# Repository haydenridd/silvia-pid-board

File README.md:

# Rancilio Silvia PID Board

A hardware and firmware project for adding PID boiler control to a stock Rancilio Silvia espresso machine.

## Obligatory Disclaimer

This project involves working with mains voltage as well as high power output heaters! Mains voltage *can kill or
seriously injure you* and improper control of an ~850W heating element *can start fires*. This project is provided
as-is with no regulatory certifications or guarantees of safety. It is on the user to do their due diligence in
ensuring their own safety, as well as the safe modification and operation of the espresso machine.

## Motivation

Adding PID heater control to the Rancilio Silvia is a popular mod, however it usually involves adding a
standalone PID controller like [this](https://www.auberins.com/index.php?main_page=product_info&products_id=36) to the
exterior of the machine. I've also seen a
number of great write-ups on home-brew mods \(so to speak\) like [this](https://misssilviapi.wordpress.com/) and
[this](https://int03.co.uk/blog/project-coffee-espiresso-machine/). However, many of the mods have
gravitated towards using various parts and modules found on Amazon, and are generally fairly invasive to the machine
itself (modules on the outside, cutting into the chassis, etc).

I had two goals with this project:
- Design a robust PID control board and source components entirely from a reputable distributor (DigiKey in this case)
- Design the board in such a way that it fits inside the machine, and leaves the control of the machine unchanged

### A Brief Aside on Amazon Parts
At the time of this writing, the electrical engineer in me would *not* consider Amazon to be a reputable retailer
for electronic parts. There have been many [reports](https://www.coffeeforums.co.uk/threads/gaggia-classic-pid-owners-watch-out-for-counterfeit-ssrs-on-ebay-amazon-etc.61314/)
of [fake parts](https://squashpractice.com/2024/01/01/counterfeits-parts-ebay-scammers-and-amazon-shills/) coming from
Amazon across all corners of industry. While these are generally ~half the price of the part they're
knocking off, you have essentially no recourse or accountability should this part fail in a catastrophic way. And
when it comes to switching AC mains and high powered heaters, that was not a gamble I was willing to take. This
project sources its parts entirely from DigiKey with the exception of a custom RTD sensor for the boiler.

## Design Ethos

I love the chunky, tactile feel of the stock Silvia machine. I wanted to leave how you control the machine entirely
unchanged. This is NOT a total conversion mod like the [Gagguino](https://gaggiuino.github.io/#/) although that project
is certainly cool. Post-mod, the machine still looks and functions largely the same to the external user, with a
small exception being how I use the heating lamp to indicate temperature status.

## Hardware Design

See [the hardware README](./silvia_pid_board/README.md) for a detailed breakdown of the electronic design, parts list,
and hookup diagram. This diagram shows the high-level design of the board:

The board, in a hacky chip board "enclosure", fits snugly in between the steam valve and the leftmost control switches:

## Firmware Design

A Raspberry Pi Pico was used for the microcontroller driving the hardware because they're cheap, and extremely well
documented. The firmware is written in [Zig](https://ziglang.org/), a fantastic up-and-coming language that I've
fallen in love with for low-level firmware development. See [the firmware README](./firmware/README.md) for more
details.

## Performance

The following shows the temperature behavior of the thermostat style regulation that comes with a stock Silvia. 

A graph of temperature over time at the espresso temperature setpoint:

And a graph of temperature of time at the steam temperature setpoint:

Compare this to the new PID regulation at the espresso setpoint:

And regulation at the steam setpoint:

Where the red line is temperature, and the blue line is duty cycle of the heater. Both of these plots can be produced
with a [script](firmware/scripts/graph_temperature.py) in the firmware folder. See that README for more details on
data logging + plotting.

Espresso setpoint regulation is extremely tight, generally regulating to within 1C. Steam regulation generally sits
~2C below the setpoint of 145C, but experimentally I found this to produce nice milk steaming pressure. Both setpoints were chosen based
on the behavior of the original thermostat + some experimental tweaking. It should be noted temperature is measured
at the exterior of the boiler, meaning a setpoint of 108C does *not* mean 108C water is going through your
espresso puck. 

## Building Your Own

All the tools you need to make one of these modules yourself are provided in this repository. I used JLPCB to build the
boards, however the gerber files located in `silvia_pid_board/board_gerbers` can be used to build boards at a PCB
fab of your preference. Note though that design rules were checked according to JLPCB's capabilities. The KiCAD design
files are also available in `silvia_pid_board` should you want to modify the board or run different design rule checks.

At the time of writing, the total BOM cost of the Digikey parts is $34. Should you choose to use the same RTD module
costing $28, and JLPCB for your fab costing ~$30 with shipping, and add some cash for shipping from Digikey, the total
cost sits ~$100 for a buildout of this. Pretty good considering an off the shelf module is ~$150! I've included the 
Digikey part numbers with the [parts list](./silvia_pid_board/parts_list.csv) where relevant, so ordering parts for
this build should be fairly straightforward.

## Closing Thoughts and Areas of Improvement

This repo is unlikely to see any major updates, and mostly serves as a write-up/how-to for anyone looking to replicate
or expand upon this project. In its current state, it does exactly what I want for my machine. However, here are some
minor things I would change if I were to do another revision of the board/firmware:
- Add a standardized SWD header to the board + route corresponding signals from the Pico for easier debugger
connection
- Solder the RP2040 + required supporting ICs directly to the board to save space rather than using the Pico board
- Add CAD designs for a 3D printable enclosure
- Implement a serial port via a USB endpoint, removing the need for a dedicated UART connection
- Expand on the CLI and logging capabilities

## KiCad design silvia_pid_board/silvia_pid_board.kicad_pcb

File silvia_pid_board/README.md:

# Hardware Design

The following outlines:
- Board circuit design
- Hookup/wiring guide
- Board mounting
- BOM/Fabrication info

## Circuit Design

A PDF of the board schematic can be found [here](./silvia_pid_board.pdf), and is useful for following along with
circuit design discussion. The circuit design for this board can be broken into the following components:
- Power supply
- AC mains switching for the boiler
- AC mains detection from the steam switch
- Heating LED control

Note that this PCB was designed with a 120VAC/60Hz mains supply in mind, and that a careful design review should be
conducted if a user wants to adapt this to a different mains input (for instance 220VAC).  

### Power Supply

Extremely simple and easy, as it is a single component, the [IRM-05](https://www.meanwellusa.com/upload/pdf/IRM-05/IRM-05-spec.pdf).
While you could probably design a switched power supply that produces 5V from AC mains voltage for a little cheaper (this part costs $7),
this part simplified a lot of headaches. Does exactly as advertised, produces a clean 5V DC from 120 VAC delivering up
to 5W of power.

### AC Mains Switching

I spent the most time and intention on this part of the design, and switching AC to the boiler (to heat it) is
accomplished with the following circuit:

This was carefully designed based on the [following application note](https://www.st.com/resource/en/application_note/an5114-controlling-a-triac-with-a-phototriac-stmicroelectronics.pdf)
from ST Micro. I will be the first to admit it's over-engineered, as it almost certainly doesn't need a snubber circuit
given it's a simple resistive load being switched. One should note that the opto-coupler used is zero-crossing, meaning
no matter when the MCU goes to switch the heater on/off, it will only switch at the zero crossing point of the AC waveform.
Note you can only switch the heater on/off as fast as the frequency of the AC input (60Hz for US), however given the
duty period of the control loop is slow (one second) it doesn't matter.

The triac used for switching is passively cooled using a board mounted heatsink. Note that experimentally this has
been plenty effective for dissapating heat, but that a redesign is likely in order if switching a higher power heater
than the Silvia's.

### AC Mains Detection

This was entirely in service of allowing the steam switch to still turn on its own integrated AC powered lamp when it
switches on/off. The following circuit:

Detects when the steam switch has been flipped "on" by detecting an AC signal. The [FOD814S](https://www.onsemi.com/download/data-sheet/pdf/fod814-d.pdf)
makes this quite easy. The `LINE_ZEROCROSS_SENSE` signal will end up being pulled to ground every time the AC signal
is over the turn-on voltage of the in-package photo-diodes. See the [firmware README](../firmware/README.md) for more
details on how this signal is used.

### Heating LED Control

The lower lamp on the power switched that is used as a heating indicator in the stock Silvia is replace by a white LED
controlled by the microcontroller. The dimensions of the chosen LED are quite similar to the stock lamp, so it was quite
easy to replace the stock lamp while preserving its housing and orange jewel lens. See the [firmware README](../firmware/README.md)
for more info on how this is used, but the general idea is a solid LED means "off target", a pulsing LED means
"close to target", and an off LED means "at target". 

## Hookup/Wiring Guide

The following is an annotated version of the electrical diagram provided with the Silvia's manual. It shows which
electrical connections have been removed or re-routed, and which signals they connect to on the PCB.

18 gauge wire was used for all AC signal level connections, and 22 gauge wire was used for all MCU signal
level connections (RTD sensor and LED).

## Board Mounting + Enclosure

Mounting holes are provided in the PCB to accomodate M3 size screws. I ended up using nylon standoffs and screws to
sandwich the board between two pieces of thick card-stock like material. 

## BOM/Fabrication

See [the following CSV](./parts_list.csv) for a full parts list for the project. The "Notes" column details whether the part goes on the
board itself, or is an ancillary part used for connections/etc.

The gerber files for getting this board fabricated are located in [board_gerbers](./board_gerbers), and pass the design
rules in `silvia_pid_board.kicad_dru` (provided by JLPCB).

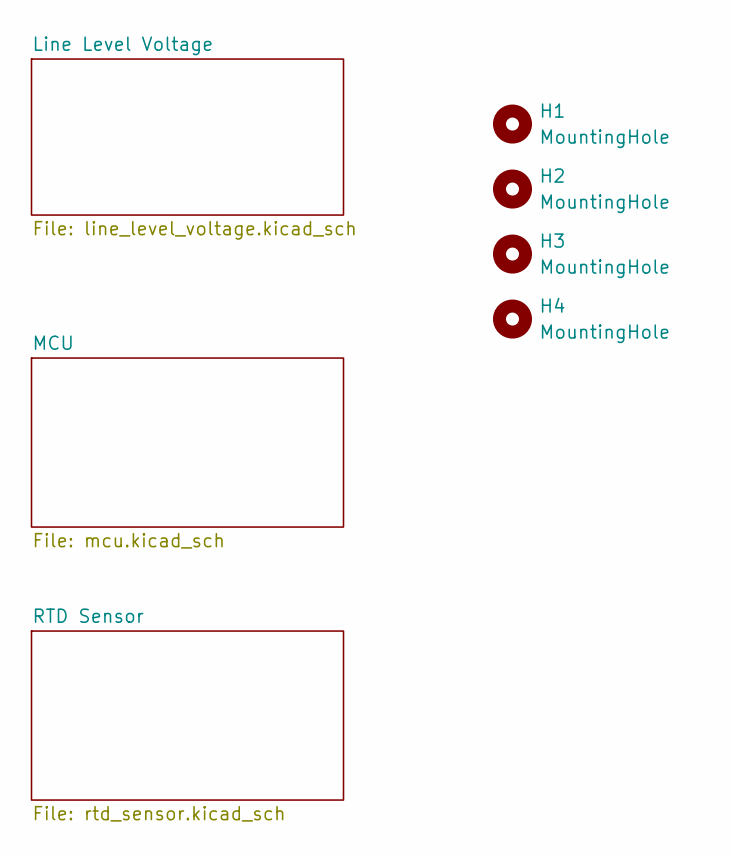
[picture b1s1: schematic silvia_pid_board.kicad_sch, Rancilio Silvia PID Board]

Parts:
H1, H2, H3, H4: MountingHole; MountingHole_3.2mm_M3_Pad_TopOnly

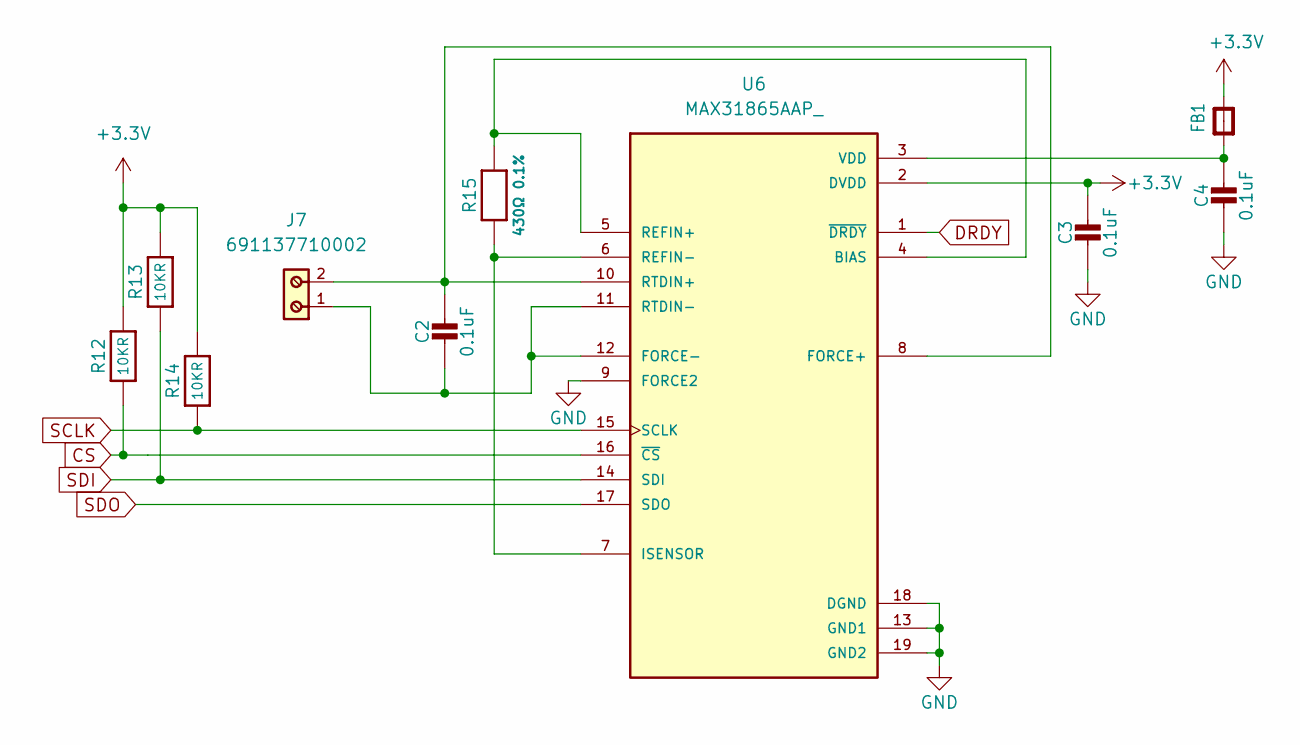
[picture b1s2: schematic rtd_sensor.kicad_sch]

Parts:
C2, C3, C4: 0.1uF; C_0805_2012Metric_Pad1.18x1.45mm_HandSolder; DIGIKEY_PN 311-1140-1-ND
FB1: FERRITE-0805NO; R_0805_2012Metric_Pad1.20x1.40mm_HandSolder; DIGIKEY_PN 490-1053-1-ND
J7: 691137710002; DIGIKEY_PN 732-10955-ND
R12, R13, R14: 10KR; R_0805_2012Metric_Pad1.20x1.40mm_HandSolder; DIGIKEY_PN 311-10KARCT-ND
R15: 430Ω 0.1%; R_0805_2012Metric_Pad1.20x1.40mm_HandSolder; DIGIKEY_PN YAG1896CT-ND
U6: MAX31865AAP_; SOP65P777X199-20N; DIGIKEY_PN MAX31865AAP+-ND

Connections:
+3.3V: C3.1, FB1.2, R12.2, R13.2, R14.2, U6.2 (DVDD); also elsewhere on the board
CS: R12.1, U6.16 (~CS); also elsewhere on the board
DRDY: U6.1 (~DRDY); also elsewhere on the board
GND: C3.2, C4.2, U6.9 (FORCE2), U6.13 (GND1), U6.18 (DGND), U6.19 (GND2); also elsewhere on the board
unnamed: C4.1, FB1.1, U6.3 (VDD)
unnamed: R15.2, U6.4 (BIAS), U6.5 (REFIN+)
unnamed: C2.1, J7.2, U6.8 (FORCE+), U6.10 (RTDIN+)
unnamed: C2.2, J7.1, U6.11 (RTDIN-), U6.12 (FORCE-)
unnamed: R15.1, U6.6 (REFIN-), U6.7 (ISENSOR)
SCLK: R14.1, U6.15 (SCLK); also elsewhere on the board
SDI: R13.1, U6.14 (SDI); also elsewhere on the board
SDO: U6.17 (SDO); also elsewhere on the board

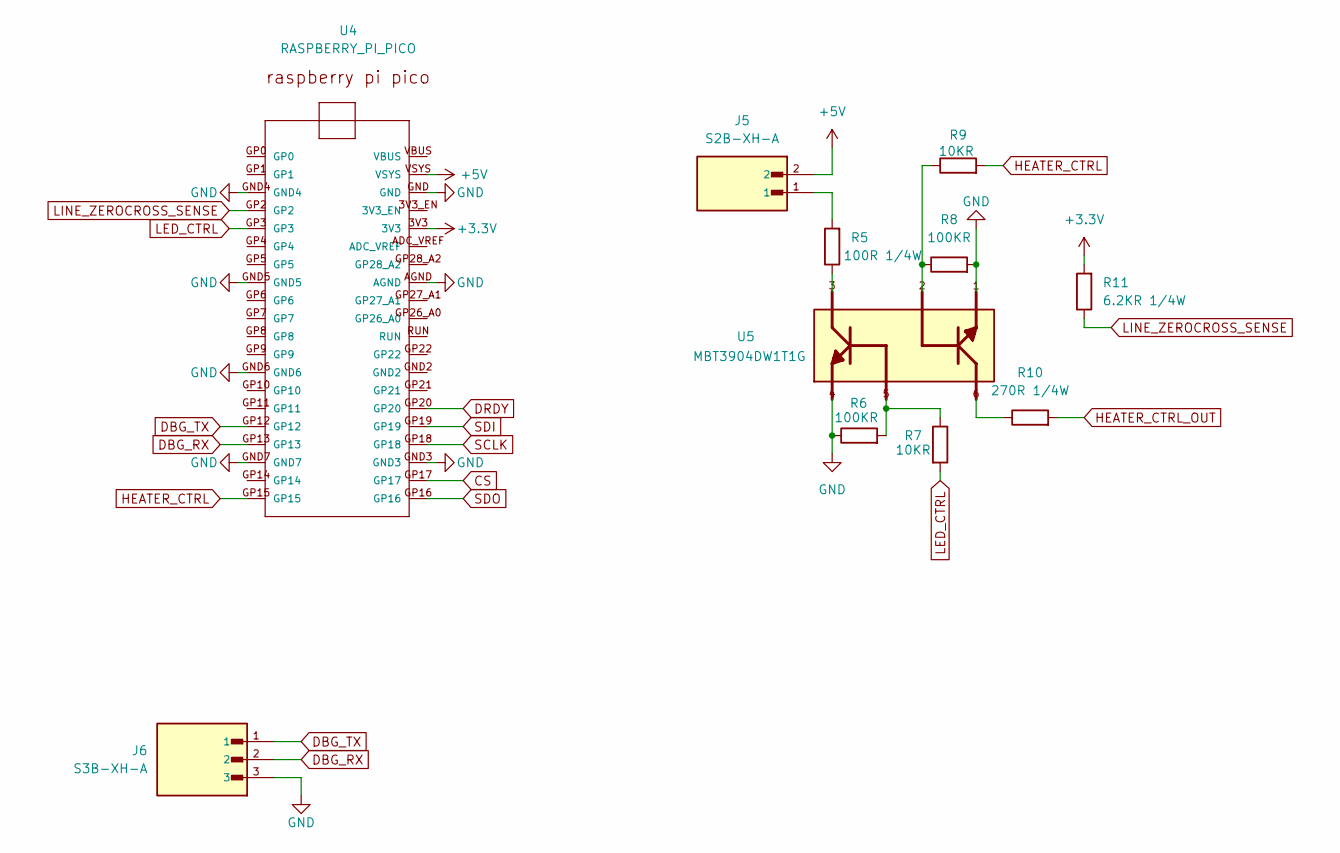
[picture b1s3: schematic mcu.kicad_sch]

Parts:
J5: S2B-XH-A; JST_S2B-XH-A; DIGIKEY_PN 455-S2B-XH-A-ND
J6: S3B-XH-A; JST_S3B-XH-A; DIGIKEY_PN 455-S3B-XH-A-ND
R5: 100R 1/4W; R_1206_3216Metric_Pad1.30x1.75mm_HandSolder; DIGIKEY_PN 311-270ERCT-ND
R6, R8: 100KR; R_0805_2012Metric_Pad1.20x1.40mm_HandSolder; DIGIKEY_PN 311-100KARCT-ND
R7, R9: 10KR; R_0805_2012Metric_Pad1.20x1.40mm_HandSolder; DIGIKEY_PN 311-10KARCT-ND
R10: 270R 1/4W; R_1206_3216Metric_Pad1.30x1.75mm_HandSolder; DIGIKEY_PN 311-270ERCT-ND
R11: 6.2KR 1/4W; R_1206_3216Metric_Pad1.30x1.75mm_HandSolder; DIGIKEY_PN 311-6.2KERCT-ND
U4: RASPBERRY_PI_PICO; DIGIKEY_PN S7053-ND(sockets),2648-SC0917-ND(pico)
U5: MBT3904DW1T1G; SOT236; DIGIKEY_PN MBT3904DW1T1GOSCT-ND

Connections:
+3.3V: R11.2, U4.3V3; also elsewhere on the board
+5V: J5.2, U4.VSYS; also elsewhere on the board
CS: U4.GP17; also elsewhere on the board
DBG_RX: J6.2, U4.GP13
DBG_TX: J6.1, U4.GP12
DRDY: U4.GP20; also elsewhere on the board
GND: J6.3, R6.1, R8.2, U4.AGND, U4.GND, U4.GND3, U4.GND4, U4.GND5, U4.GND6, U4.GND7, U5.1, U5.4; also elsewhere on the board
HEATER_CTRL: R9.2, U4.GP15
HEATER_CTRL_OUT: R10.2; also elsewhere on the board
LED_CTRL: R7.2, U4.GP3
LINE_ZEROCROSS_SENSE: R11.1, U4.GP2; also elsewhere on the board
unnamed: J5.1, R5.2
unnamed: R5.1, U5.3
unnamed: R6.2, R7.1, U5.5
unnamed: R8.1, R9.1, U5.2
unnamed: R10.1, U5.6
SCLK: U4.GP18; also elsewhere on the board
SDI: U4.GP19; also elsewhere on the board
SDO: U4.GP16; also elsewhere on the board

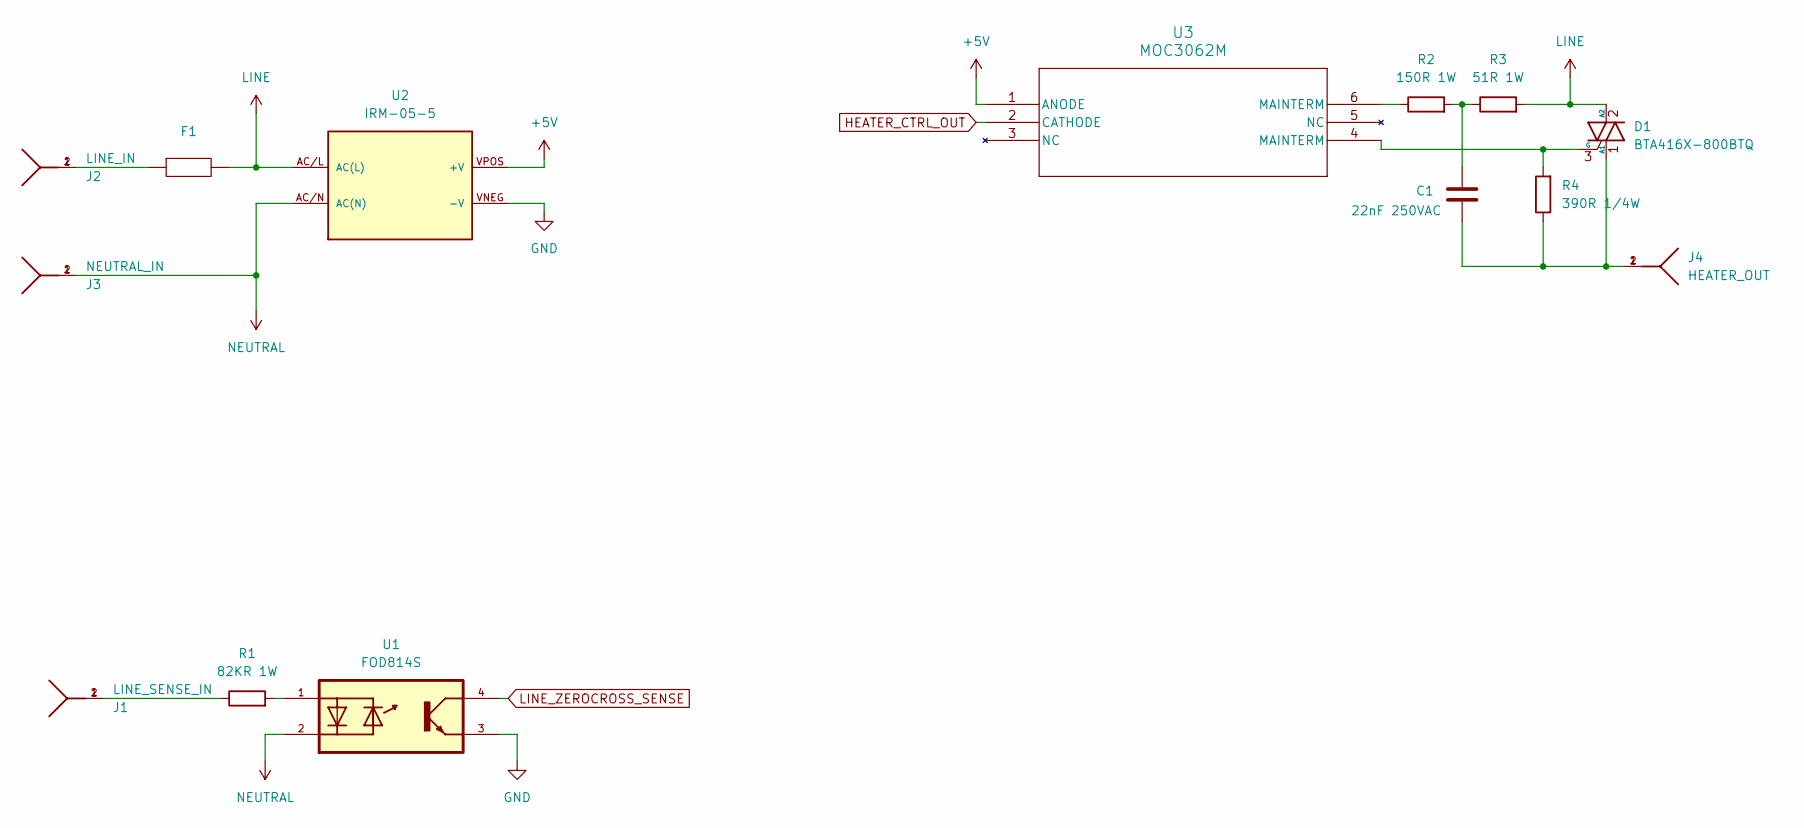
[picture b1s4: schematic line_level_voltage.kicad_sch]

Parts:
C1: 22nF 250VAC; C_1808_4520Metric_Pad1.72x2.30mm_HandSolder; PARTREV 11-Oct-17; DIGIKEY_PN 399-CAN17C223KARACTUCT-ND
D1: BTA416X-800BTQ; to220_with_heatsink; DIGIKEY_PN 1740-BTA416X-800BTQ-ND(Triac), HS403-ND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
F1: fuse_holder; DIGIKEY_PN 36-3521-ND (Holders),0225010.MXP-ND (Fu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
J1: LINE_SENSE_IN; CONN_63824-1; PARTREV R; DIGIKEY_PN A29938CT-ND
J2: LINE_IN; CONN_63824-1; PARTREV R; DIGIKEY_PN A29938CT-ND
J3: NEUTRAL_IN; CONN_63824-1; PARTREV R; DIGIKEY_PN A29938CT-ND
J4: HEATER_OUT; CONN_63824-1; PARTREV R; DIGIKEY_PN A29938CT-ND
R1: 82KR 1W; R_2512_6332Metric_Pad1.40x3.35mm_HandSolder; DIGIKEY_PN 13-RC2512JK-0782KLCT-ND
R2: 150R 1W; R_2512_6332Metric_Pad1.40x3.35mm_HandSolder; DIGIKEY_PN 13-SR2512JK-07150RLCT-ND
R3: 51R 1W; R_2512_6332Metric_Pad1.40x3.35mm_HandSolder; DIGIKEY_PN 13-AC2512JK-0751RLCT-ND
R4: 390R 1/4W; R_1206_3216Metric_Pad1.30x1.75mm_HandSolder; DIGIKEY_PN 311-390ERCT-ND
U1: FOD814S; SOIC254P1016X385-4N; DIGIKEY_PN FOD814S-ND
U2: IRM-05-5; CONV_IRM-05-5; DIGIKEY_PN 1866-3027-ND
U3: MOC3062M; PDIP6_8P89X6P6_ONS; DIGIKEY_PN MOC3062M-ND

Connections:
+5V: U2.VPOS (+V), U3.1 (ANODE); also elsewhere on the board
GND: U1.3, U2.VNEG (-V); also elsewhere on the board
HEATER_CTRL_OUT: U3.2 (CATHODE); also elsewhere on the board
LINE: D1.2 (A2), F1.3, F1.4, R3.2, U2.AC/L (AC(L))
LINE_ZEROCROSS_SENSE: U1.4; also elsewhere on the board
NEUTRAL: J3.1, J3.2, U1.2, U2.AC/N (AC(N))
unnamed: C1.1, R2.2, R3.1
unnamed: C1.2, D1.1 (A1), J4.1, J4.2, R4.1
unnamed: D1.3 (G), R4.2, U3.4 (MAINTERM)
unnamed: F1.1, F1.2, J2.1, J2.2
unnamed: J1.1, J1.2, R1.1
unnamed: R1.2, U1.1
unnamed: R2.1, U3.6 (MAINTERM)

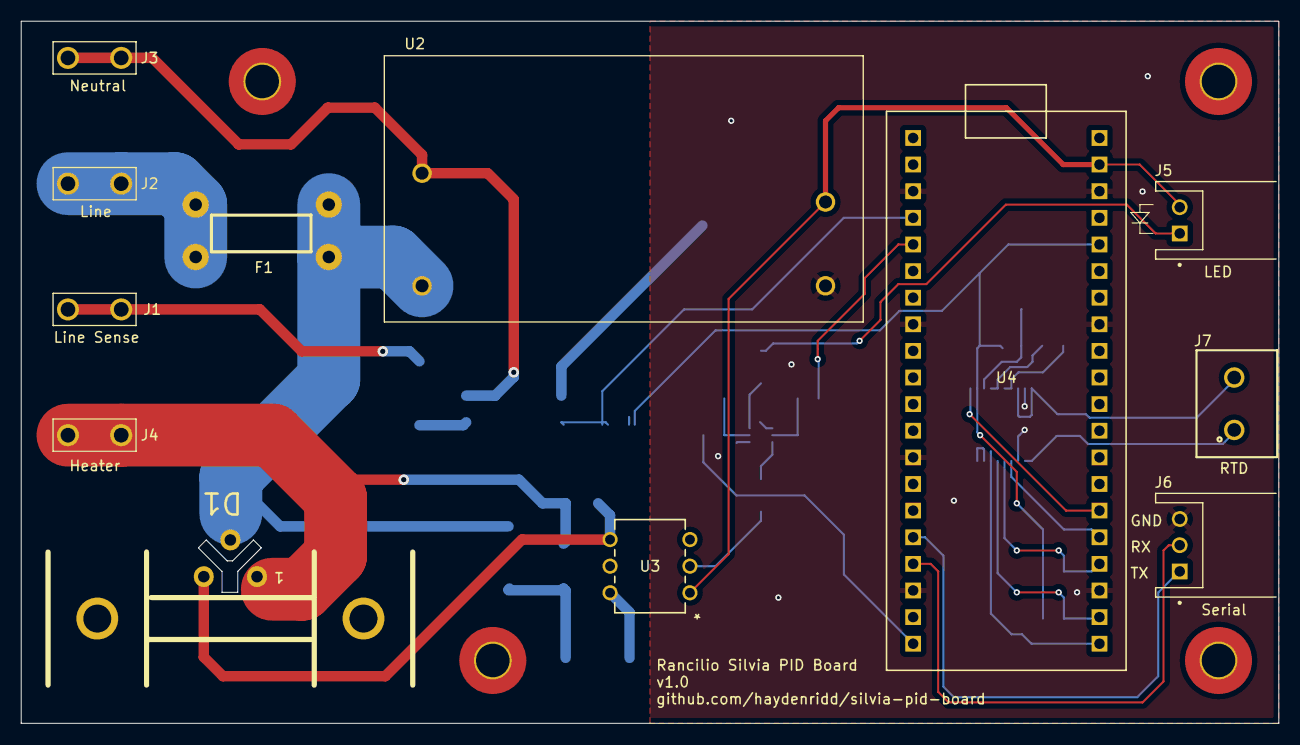
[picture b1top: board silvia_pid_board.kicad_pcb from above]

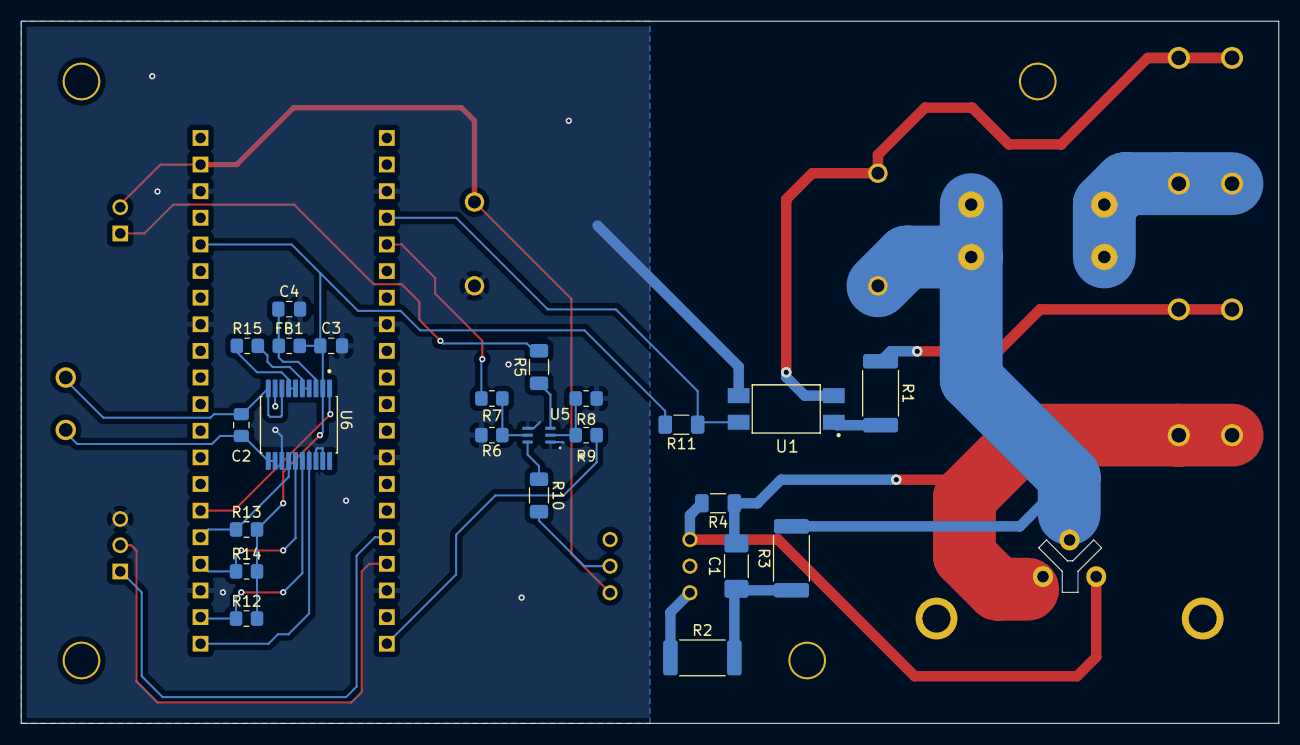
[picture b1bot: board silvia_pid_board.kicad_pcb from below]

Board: 2 copper layers, 120.0 x 67.0 mm, 39 parts (23 on the bottom side), 33 nets.

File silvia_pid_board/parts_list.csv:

Reference,Value,Qty,DIGIKEY_PN,Notes
C1,22nF 250VAC,1,399-CAN17C223KARACTUCT-ND,Board Component
"C2,C3,C4",0.1uF,3,311-1140-1-ND,Board Component
D1,BTA416X-800BTQ,1,1740-BTA416X-800BTQ-ND,Board Component
D1,Heatsink,1,HS403-ND,Board Component
F1,Fuse Holder,1,36-3521-ND,Board Component
F1,Fuse,1,0225010.MXP-ND,Board Component
FB1,FERRITE-0805NO,1,490-1053-1-ND,Board Component
J1,LINE_SENSE_IN,1,A29938CT-ND,Board Component
J2,LINE_IN,1,A29938CT-ND,Board Component
J3,NEUTRAL_IN,1,A29938CT-ND,Board Component
J4,HEATER_OUT,1,A29938CT-ND,Board Component
J5,S2B-XH-A,1,455-S2B-XH-A-ND,Board Component
J6,S3B-XH-A,1,455-S3B-XH-A-ND,Board Component
J7,691137710002,1,732-10955-ND,Board Component
R1,82KR 1W,1,13-RC2512JK-0782KLCT-ND,Board Component
R2,150R 1W,1,13-SR2512JK-07150RLCT-ND,Board Component
R3,51R 1W,1,13-AC2512JK-0751RLCT-ND,Board Component
R4,390R 1/4W,1,311-390ERCT-ND,Board Component
R5,100R 1/4W,1,311-270ERCT-ND,Board Component
"R6,R8",100KR,2,311-100KARCT-ND,Board Component
"R7,R9,R12,R13,R14",10KR,5,311-10KARCT-ND,Board Component
R10,270R 1/4W,1,311-270ERCT-ND,Board Component
R11,6.2KR 1/4W,1,311-6.2KERCT-ND,Board Component
R15,430Ω  0.1%,1,YAG1896CT-ND,Board Component
U1,FOD814S,1,FOD814S-ND,Board Component
U2,IRM-05-5,1,1866-3027-ND,Board Component
U3,MOC3062M,1,MOC3062M-ND,Board Component
U4,RASPBERRY_PI_PICO,1,2648-SC0917-ND,Board Component
U5,MBT3904DW1T1G,1,MBT3904DW1T1GOSCT-ND,Board Component
U6,MAX31865AAP_,1,MAX31865AAP+-ND,Board Component
~,https://www.auberins.com/index.php?main_page=product_info&pr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,1,~,Custom RTD sensor that fits in thermostat clip
~,XHP-2,1,455-2266-ND,2 position connector for RTD sensor port
~,XHP-3,1,455-2219-ND,3 position connector for UART port
~,2-520263-2,4,A27821CT-ND,AMP connectors for connecting AC signals to board
~,PPPC201LFBN-RC,2,S7053-ND,Female headers for Rpi Pico
~,SXH-001T-P0.6N,5,455-4220-100-ND,Crimp connectors
~,INL-3AW30,1,1830-1006-ND,White LED for temperature lamp indicator replacement

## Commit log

2025-10-07 - Upload project
2025-10-07 - Some README updates
2025-10-07 - Added gerber files
2025-10-07 - Added schematic pdf
2025-10-07 - Small clarification on temperature regulation
